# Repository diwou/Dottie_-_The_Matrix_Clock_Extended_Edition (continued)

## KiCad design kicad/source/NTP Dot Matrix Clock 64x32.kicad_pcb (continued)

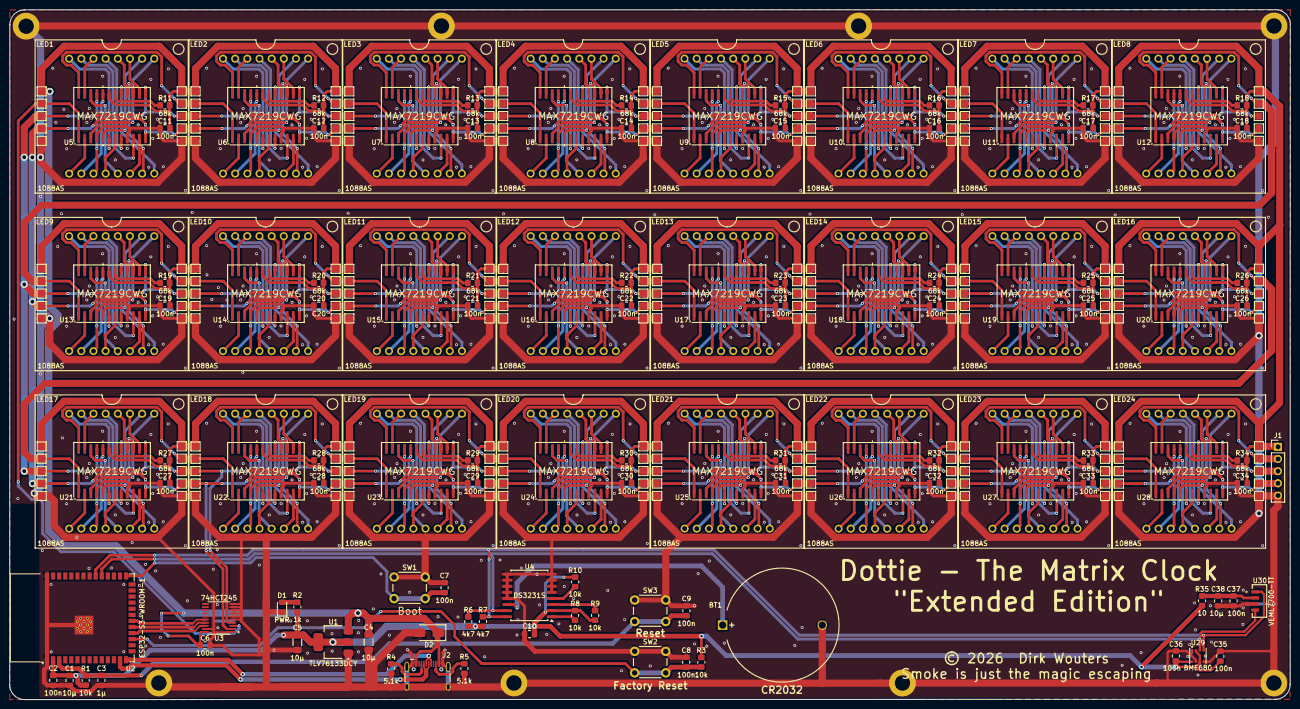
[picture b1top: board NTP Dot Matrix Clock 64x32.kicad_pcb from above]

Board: 2 copper layers, 267.4 x 144.1 mm, 383 parts (0 on the bottom side), 456 nets.

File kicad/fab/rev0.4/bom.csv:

Designator,Footprint,Quantity,Value,LCSC Part #
BT1,BatteryHolder_MYOUNG_BS-07-A1BJ001_CR2032,1,CR2032,
"C1, C38",0805,2,10µ,
"C10, C11, C12, C13, C14, C15, C16, C17, C18, C19, C2, C20, C21, C22, C23, C24, C25, C26, C27, C28, C29, C30, C31, C32, C33, C34, C35, C36, C37, C6, C7, C8, C9",0805,33,100n,
C3,0805,1,1µ,
"C4, C5",1206,2,10µ,
D1,0805,1,PWR,
D2,D_SMA,1,SS14,
J1,PinHeader_1x05_P2.54mm_Vertical,1,Conn_01x05,
"J10, J100, J101, J102, J103, J104, J105, J106, J107, J108, J109, J11, J110, J111, J112, J113, J114, J115, J116, J117, J118, J119, J12, J120, J121, J122, J123, J124, J125, J126, J127, J128, J129, J13, J130, J131, J132, J133, J134, J135, J136, J137, J138, J139, J14, J140, J141, J142, J143, J144, J145, J146, J147, J148, J149, J15, J150, J151, J152, J153, J154, J155, J156, J157, J158, J159, J16, J160, J161, J162, J163, J164, J165, J166, J167, J168, J169, J17, J170, J171, J172, J173, J174, J175, J176, J177, J178, J179, J18, J180, J181, J182, J183, J184, J185, J186, J187, J188, J189, J19, J190, J191, J192, J193, J194, J195, J196, J197, J198, J199, J20, J200, J201, J202, J203, J204, J205, J206, J207, J208, J209, J21, J210, J211, J212, J213, J214, J215, J216, J217, J218, J219, J22, J220, J221, J222, J223, J224, J225, J226, J227, J228, J229, J23, J230, J231, J232, J233, J234, J235, J236, J237, J238, J239, J24, J240, J241, J242, J25, J26, J27, J28, J29, J3, J30, J31, J32, J33, J34, J35, J36, J37, J38, J39, J4, J40, J41, J42, J43, J44, J45, J46, J47, J48, J49, J5, J50, J51, J52, J53, J54, J55, J56, J57, J58, J59, J6, J60, J61, J62",TestPoint_Pad_1.5x1.5mm,200,Conn_01x01_Pin,
J2,USB_C_Receptacle_HCTL_HC-TYPE-C-16P-01A,1,USB_C_Receptacle_USB2.0_16P,
"J63, J64, J65, J66, J67, J68, J69, J7, J70, J71, J72, J73, J74, J75, J76, J77, J78, J79, J8, J80, J81, J82, J83, J84, J85, J86, J87, J88, J89, J9, J90, J91, J92, J93, J94, J95, J96, J97, J98, J99",TestPoint_Pad_1.5x1.5mm,40,Conn_01x01_Pin,
"LED1, LED10, LED11, LED12, LED13, LED14, LED15, LED16, LED17, LED18, LED19, LED2, LED20, LED21, LED22, LED23, LED24, LED3, LED4, LED5, LED6, LED7, LED8, LED9",LED_1088_Pin_Header,24,1088AS,
"R1, R10, R3, R8, R9",0805,5,10k,
"R11, R12, R13, R14, R15, R16, R17, R18, R19, R20, R21, R22, R23, R24, R25, R26, R27, R28, R29, R30, R31, R32, R33, R34",0805,24,68k,
R2,0805,1,1k,
R35,0805,1,10,
"R4, R5",0805,2,5.1k,
"R6, R7",0805,2,4k7,
SW1,SW_PUSH_6mm_H5mm,1,Boot,
SW2,SW_PUSH_6mm_H5mm,1,Factory Reset,
SW3,SW_PUSH_6mm_H5mm,1,Reset,
U1,SOT-223-3_TabPin2,1,TLV76133DCY,
"U10, U11, U12, U13, U14, U15, U16, U17, U18, U19, U20, U21, U22, U23, U24, U25, U26, U27, U28, U5, U6, U7, U8, U9",SOIC-24W_7.5x15.4mm_P1.27mm,24,MAX7219CWG,
U2,ESP32-S3-WROOM-1,1,ESP32-S3-WROOM-1,
U29,Bosch_LGA-8_3x3mm_P0.8mm_ClockwisePinNumbering,1,BME680,
U3,TSSOP-20_4.4x6.5mm_P0.65mm,1,74HCT245,
U30,XDCR_VEML7700-TT,1,VEML7700-TT,
U4,SOIC-16W_7.5x10.3mm_P1.27mm,1,DS3231S,

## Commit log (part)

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2026-05-13 feat: initialisiere dottie extended version
2026-05-13 fix: vervollstaendige font fuer wochentagsanzeige
2026-05-13 fix: setze echten 6x7-font und direkte helligkeitsanwendung um
2026-05-13 fix: korrigiere 6x7-modulfont und helligkeit auf allen modulen
2026-05-13 fix: nutze 8x8-font fuer wochentagsanzeige 1zu1
2026-05-13 fix: SPI-Race-Condition zwischen Web-Task und Haupt-Loop behoben
    Helligkeits- und PWM-Änderungen aus dem Webinterface werden nicht
    mehr direkt im Web-Task per mx.control() auf die MAX7219 geschrieben,
    sondern über Deferred-Flags sicher im Haupt-Loop verarbeitet.
    Behebt zufällige Pixelfehler und ungleichmäßige Helligkeit besonders
    bei Sprung von dunkel (0) auf hell (10-15).
2026-05-13 docs: referenz fuer spi-race-fix im changelog ergaenzt
2026-05-13 fix: dritte Modulreihe beim OTA-Update löschen
2026-05-13 docs: referenz fuer ota-3te-reihe-fix im changelog ergaenzt
2026-05-13 feat: u8g2-proportionalschrift fuer wochentagsanzeige
    Dritte Modulreihe (Wochentag) nutzt jetzt u8g2_font_helvR08_tf
    als proportionalschrift. U8g2 rendert in einen offscreen-buffer
    (keine SPI-konkurrenz mit MD_MAX72XX); pixel werden via rowSet()
    auf die unteren MAX7219-module kopiert.
2026-05-13 docs: referenz fuer u8g2-proportionalschrift im changelog ergaenzt
2026-05-13 fix: u8g2-buffer spaltenweise auslesen und baseline korrigiert
    Der MAX7219-Treiber in U8g2 nutzt u8g2_ll_hvline_vertical_top_lsb,
    der den Buffer spaltenweise organisiert (buf[col] = 8 vertikale
    Pixel). Behebt die 'zufaelligen Pixel' bei der Wochentagsanzeige.
    Baseline von y=8 auf y=7 korrigiert fuer 8px-Fonthoehe.
2026-05-13 fix: buffer-layout auf horizontal_right_lsb korrigiert
    u8g2_Setup_max7219_64x8_f verwendet horizontal_right_lsb:
    buf[row*8 + tile] mit Maske 0x80>>col (MSB=linkes Pixel).
    Nicht vertical_top_lsb.
2026-05-13 fix: u8g2-baseline auf y=8 fuer vollstaendige 8px-darstellung
2026-05-13 fix: u8g2-font auf _tr variante ohne kerning
2026-05-13 fix: font auf ncenR08 (new century schoolbook) fuer bessere laufweite
2026-05-13 feat: schriftart und gross-/kleinschreibung fuer wochentag umschaltbar
    Web-UI: Font-Select (6 Schriftarten) + Checkbox fuer gemischte
    Gross-/Kleinschreibung im Display-Tab. Konfiguration wird
    persistent gespeichert.
2026-05-13 docs: u8g2-schriftauswahl und case-toggle im changelog dokumentiert
2026-05-13 fix: ntp-subsekunden und rundtrip-delay bei zeitsync kompensieren
    ntpProbeOnce und ntpProbeByIp lesen jetzt den fractional-teil
    der transmit-timestamp (bytes 44-47) und addieren die halbe
    round-trip-zeit. txSec wird auf naechste ganze sekunde gerundet.
    Behebt den ~1-sekunden-nachlauf der uhrzeit.
2026-05-13 docs: referenz fuer ntp-subsekunden-fix im changelog ergaenzt
2026-05-13 fix: scroll-animation vereinfacht, subsekunden-kompensation entfernt
    Die gettimeofday-basierte Subsekunden-Kompensation konnte auf
    ESP32 zu uninitialisierten Werten und damit zu quasi sofortigem
    Animationsende fuehren. Stattdessen immer volle 12 Schritte (240ms).
2026-05-14 fix: datei webserver.h in ClockWebUi.h umbenannt, um windows-namenskonflikt mit WebServer.h zu beheben
2026-05-14 docs: changelog-referenz fuer webserver-umbenennung ergaenzt
2026-05-14 chore: AGENTS.md aus Repository entfernt, .gitattributes fuer Zeilenenden-Normalisierung angelegt
2026-05-14 docs: changelog-referenz fuer gitattributes-commit ergaenzt
2026-05-15 fix: ntp-subsekunden-genauigkeit durch sekundengrenz-sync verbessert
    Vor dem RTC-Schreiben wird jetzt gezielt auf die naechste volle
    Sekundengrenze gewartet, damit die RTC exakt zur Sekundenmitte
    loslaeuft. Eliminiert den variablen Subsekunden-Versatz zwischen
    mehreren unabhaengig synchronisierten Uhren.
2026-05-15 docs: commit-id im changelog fuer sekundengrenz-fix korrigiert
2026-05-26 refactor: modernize architecture (asynchronous sntp, event-driven wifi, system time)
    - Switch to native ESP32 SNTP and internal system time
    - Replace blocking WiFi loops with event handlers
    - Remove jittery software PWM and redundant I2C polling
    - Optimize main loop for stability and smoothness
    - Update Web UI to reflect architectural changes
2026-05-26 docs: add commit reference to changelog for architectural refactor
2026-05-26 refactor: update time source status labels for clarity
    Change 'DS3231 active' to 'ESP32 (RTC)' and 'NTP active' to 'ESP32 (NTP)' to better reflect that the internal ESP32 clock is the primary source while indicating its sync status.
2026-05-27 fix: redraw separators after display clear by invalidating scroll cache
2026-05-27 docs: add commit reference to changelog for separator fix
2026-06-04 fix: korrigierte Platine V0.5
2026-06-04 .geminipolicy.json gelöscht
2026-06-04 build.log gelöscht
2026-06-04 build-utf8.log gelöscht
2026-06-06 feat: BME680 Umweltdaten in Web-UI anzeigen
2026-06-06 docs: Changelog für BME680 Umweltdaten aktualisiert
2026-06-06 docs: Changelog-Referenz korrigiert und .gitignore aktualisiert
2026-06-06 feat: einfacher IAQ-Index für BME680 implementiert
2026-06-06 docs: Changelog für IAQ-Index aktualisiert
2026-06-06 feat: Umweltdaten-Scrolltext in 3. Zeile implementiert
2026-06-06 docs: Changelog und CSpell für Umweltdaten-Scrolltext aktualisiert
2026-06-06 fix: Grad-Symbol Encoding für Display korrigiert
2026-06-06 fix: Flackern behoben und Font-Wiederherstellung korrigiert
2026-06-06 fix: Scrolltext läuft im Wechselmodus nun immer komplett durch
2026-06-06 fix: Wechsel-Intervall und Font-Selection in 3. Zeile korrigiert
2026-06-06 fix: vertikaler Offset des Scrolltexts korrigiert
2026-06-06 feat: separater Font für Umweltdaten konfigurierbar
2026-06-06 fix: U8g2 UTF8 API korrekt eingebunden und Scroll-Stottern behoben
2026-06-06 fix: Grad-Symbol durch 'tf'-Fonts reaktiviert und Scroll-Stottern durch Task-Offloading behoben
2026-06-06 feat: Backend für 24h-Umweltdaten-Historie implementiert
2026-06-06 fix: SVG-Escaping im JavaScript korrigiert
2026-06-06 docs: Changelog für Umweltdaten-Visualisierung aktualisiert
2026-06-06 feat: Anzeige des letzten Speicherzeitpunkts der Historie
2026-06-06 feat: Zeitindex und Gitterlinien für Historie-Charts hinzugefügt
2026-06-06 fix: Überlappung der Chart-Beschriftungen behoben
2026-06-07 fix: Systemstabilität durch Task-Trennung und optimiertes JSON-Streaming verbessert
2026-06-07 fix: Syntaxfehler und Funktions-Umbenennungen korrigiert
2026-06-07 fix: Chart-Skalierung auf feste 24h korrigiert
2026-06-07 feat: Hostname im Webinterface konfigurierbar gemacht
2026-06-07 docs: Changelog für konfigurierbaren Hostnamen aktualisiert
2026-06-07 fix: Systemstabilität durch I2C-Mutex und optimierte Tasks verbessert; NTP-Sync Anzeige korrigiert
2026-06-07 fix: Deadlock in setup() durch Umstellung auf rekursiven Mutex behoben
2026-06-07 fix: BME680 Gasmessung durch Heizelement-Konfiguration reaktiviert
2026-06-07 fix: BME680 Stabilisierungsphase (3 Min) für genauere IAQ-Baseline eingeführt
2026-06-09 fix: BME680 Konfiguration und Baseline-Persistenz korrigiert
2026-06-09 docs: Changelog für BME680-Fixes und Deadlock-Korrektur ergänzt
2026-06-09 feat: BME680-Baseline in WebUI und Projektregeln-Hinweis in Changelog
2026-06-09 chore: release v1.6.0
2026-06-09 chore: release v1.7.0
2026-06-09 chore: begin development on v1.8.0-dev
2026-06-09 feat(release): automate codeberg api upload script
2026-06-10 fix(iaq): implement dynamic baseline decay and littlefs persistence
2026-06-10 docs: update CHANGELOG for IAQ fix
2026-06-10 feat: implement 30-day tag/nacht history and UI
2026-06-10 fix(ui): render empty month charts properly
2026-06-10 fix(version): revert base version to 1.7.0-dev
2026-06-10 fix(bme680): clamp iaq score to 0-500 to prevent false 'stabilizing' state
2026-06-11 fix(ui): draw circles on 30-day history graph to make single days visible
2026-06-11 fix(iaq): baseline max tracking and score limits
2026-06-17 feat(iaq): add ema filter for smoother iaq score rendering
2026-06-19 feat(ui): add humidity status text and pressure trend arrow
2026-06-19 feat(iaq): use 5min average for 24h history chart
2026-06-19 fix(iaq): replace 5min average with dedicated 99% diagram EMA filter and fix -1.0 plot bug
2026-06-21 feat(env): add dew point, heat index, and weather forecast
2026-06-21 feat(env): add absolute humidity, mold warning, sea level pressure and fix i2c diag ui
2026-06-21 fix(ui): resolve duplicate i2c html id and add NN label
2026-06-21 feat(env): add qualitative indicator for absolute humidity
2026-06-21 fix(config): add elevation to load and save routines in flash
2026-06-22 feat(display): add weather forecast and absolute humidity status to matrix scrolltext
2026-06-22 style(display): convert matrix scrolltext indicators to uppercase and use umlauts
2026-06-22 fix(display): remove umlauts from uppercase matrix scrolltext to prevent top cutoff
2026-06-22 chore: add missing commit refs to changelog
2026-06-22 fix(memory): replace String allocations in matrix loop with static char array to prevent LwIP heap fragmentation and network crashes
2026-06-22 fix(ntp): set sync error indicator exactly 5 minutes after configured interval to allow router reboot grace period
2026-06-22 style(env): replace weather trend categories with user suggested terminology
2026-06-22 chore: update changelog for weather trend terminology
2026-06-23 feat: add IBM BIOS 8x8 font (ib8x8u_tf) and revert env labels to mixed case to test lowercase rendering
2026-06-23 fix: correct font index limit in display.h to 6
2026-06-23 fix: change IBM font from VGA to CGA to ensure exact 8x8 bounding box
2026-06-23 feat: implement custom user ibm 8x8 font converted from .ino
2026-06-23 docs: update changelog with custom font implementation
2026-06-23 feat: Add absolute humidity graph with colored zones to WebUI
